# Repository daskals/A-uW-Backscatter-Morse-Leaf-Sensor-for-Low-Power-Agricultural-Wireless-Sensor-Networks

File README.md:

# A uW Backscatter-Morse-Leaf Sensor for Low-Power Agricultural Wireless Sensor Networks
Design files of IEEE publication: A uW Backscatter-Morse-Leaf Sensor for Low-Power Agricultural Wireless Sensor Networks

Nowadays, the monitoring of plant water stress
is of high importance in smart agriculture. Instead of the
traditional ground soil-moisture measurement, leaf sensing is a
new technology, which is used for the detection of plants needing
water. In this work, a novel, low-cost and low-power system for
leaf sensing using a new plant backscatter sensor node/tag is
presented. The latter, can result in the prevention of water waste
(water-use efficiency), when is connected to an irrigation system.
Specifically, the sensor measures the temperature differential
between the leaf and the air, which is directly related to the plant
water stress. Next, the tag collects the information from the leaf
sensor through an analog-to-digital converter (ADC), and then,
communicates remotely with a low-cost software-defined radio
(SDR) reader using monostatic backscatter architecture. The tag
consists of the sensor board, a microcontroller, an external timer
and an RF front-end for communication. The timer produces a
subcarrier frequency for simultaneous access of multiple tags.
The proposed work could be scaled and be a part of a large
backscatter wireless sensor network (WSN). The communication
protocol exploits the low-complexity Morse code modulation on
a 868 MHz carrier signal. The presented novel proof-of-consent
prototype is batteryless and was powered by a flexible solar panel
consuming power around 20 µW. The performance was validated
in an indoors environment where wireless communication was
successfully achieved up to 2 m distance.

**Authors:**

Spyridon Nektarios Daskalakis\
Stylianos D. Assimonis\
George Goussetis\
Manos M. Tentzeris\
Apostolos Georgiadis

---
IEEE Xplore: https://ieeexplore.ieee.org/document/8423620 \
Local: http://daskalakispiros.com/files/daskalalakis_sensors_2018.pdf

---

---
**Questions/issues**
Inquiries regarding the scripts provided are cordially welcome.

---
**Citing**

If you use our design, please cite [[1]](https://ieeexplore.ieee.org/document/8423620).

```bibtex
@article{daskalakis2018uw,
  title={A uW backscatter-morse-leaf sensor for low-power agricultural wireless sensor networks},
  author={Daskalakis, Spyridon Nektarios and Goussetis, George and Assimonis, Stylianos D and Tentzeris, Manos M and Georgiadis, Apostolos},
  journal={IEEE Sensors Journal},
  volume={18},
  number={19},
  pages={7889--7898},
  year={2018},
  publisher={IEEE}
}
 
```

[[1]](https://ieeexplore.ieee.org/document/8423620) S. N. Daskalakis, G. Goussetis, S. D. Assimonis, M. M. Tentzeris and A. Georgiadis, A uW Backscatter-Morse-Leaf Sensor for Low Power Agricultural Wireless Sensor Networks, IEEE Sensors Journal, Vol. 18, No. 19, pp. 7889–7898, Oct. 2018.

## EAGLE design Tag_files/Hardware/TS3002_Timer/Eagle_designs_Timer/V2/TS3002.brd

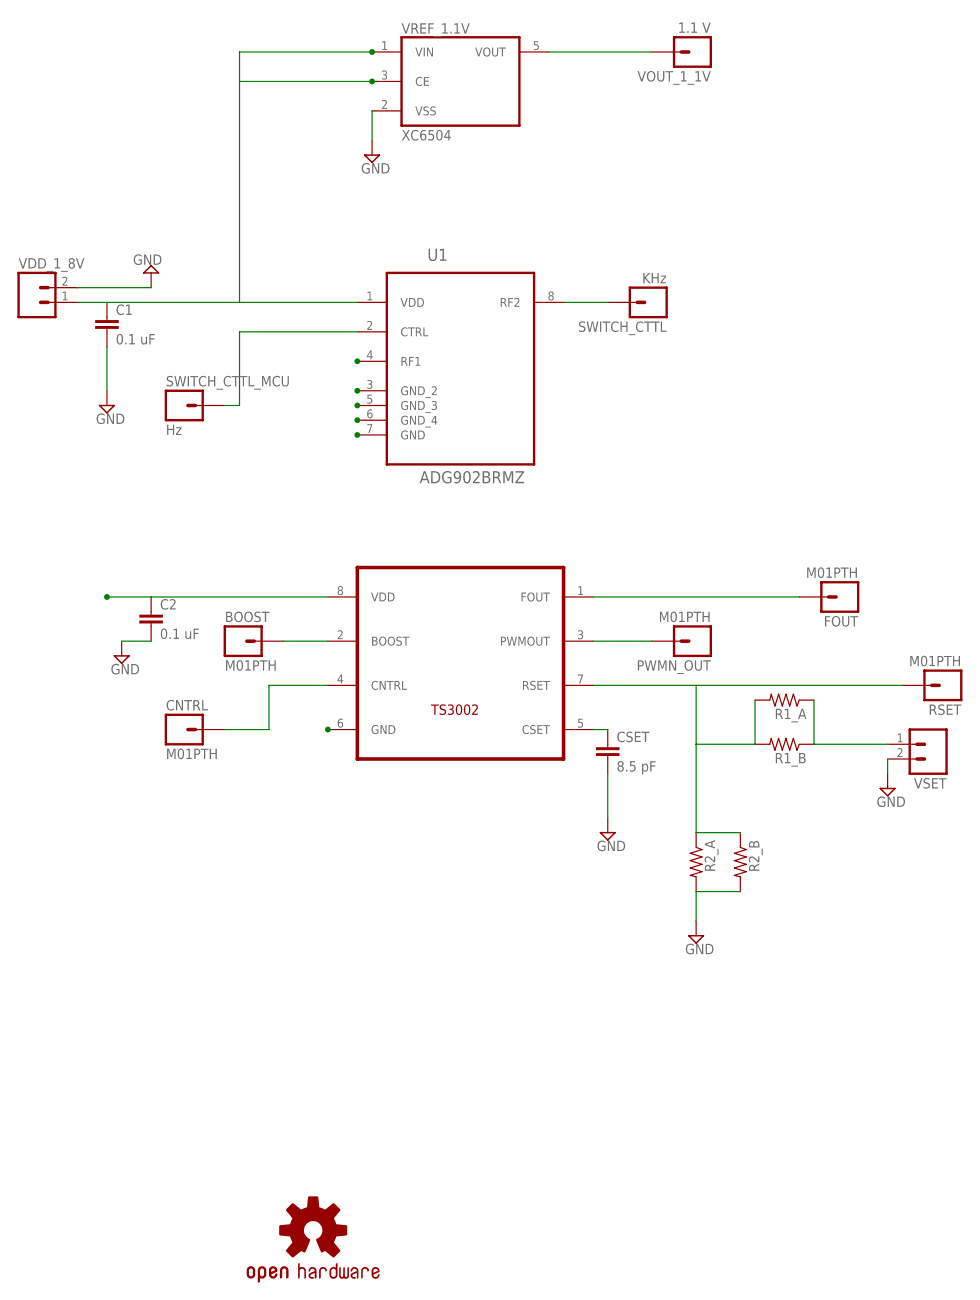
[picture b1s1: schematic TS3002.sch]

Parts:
BOOST: M01PTH; 1X01
C1, C2: 0.1 uF; 0603-CAP
CNTRL: M01PTH; 1X01
CSET: 8.5 pF; 0603-CAP
FOUT: M01PTH; 1X01
LOGO1: OSHW-LOGOL; OSHW-LOGO-L
PWMN_OUT: M01PTH; 1X01
R1_A, R1_B, R2_A, R2_B: RESISTOR0603-RES; 0603-RES
RSET: M01PTH; 1X01
SWITCH_CTTL: KHz; 1X01
SWITCH_CTTL_MCU: Hz; 1X01
U1: ADG902BRMZ; SOP65P490X110-8N
U$1: TS3002; TDFN22-8
VDD_1_8V: M02PTH; 1X02
VOUT_1_1V: 1.1 V; 1X01
VREF_1.1V: XC6504; SOT23-5
VSET: M02PTH; 1X02

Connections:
1_2OUT: C2.1, U$1.8 (VDD), VOUT_1_1V.1, VREF_1.1V.5 (VOUT)
GND: C1.2, C2.2, CSET.2, R2_A.2, R2_B.2, U1.3 (GND_2), U1.5 (GND_3), U1.6 (GND_4), U1.7 (GND), U$1.6 (GND), VDD_1_8V.2, VREF_1.1V.2 (VSS), VSET.2
unnamed: R1_A.1, R1_B.1, VSET.1
unnamed: SWITCH_CTTL_MCU.1, U1.2 (CTRL)
unnamed: BOOST.1, U$1.2 (BOOST)
unnamed: SWITCH_CTTL.1, U1.8 (RF2)
unnamed: CNTRL.1, U$1.4 (CNTRL)
unnamed: R1_A.2, R1_B.2, R2_A.1, R2_B.1, RSET.1, U$1.7 (RSET)
unnamed: PWMN_OUT.1, U$1.3 (PWMOUT)
unnamed: CSET.1, U$1.5 (CSET)
TIMER: FOUT.1, U1.4 (RF1), U$1.1 (FOUT)
VDD_1.8V1: C1.1, U1.1 (VDD), VDD_1_8V.1, VREF_1.1V.1 (VIN), VREF_1.1V.3 (CE)

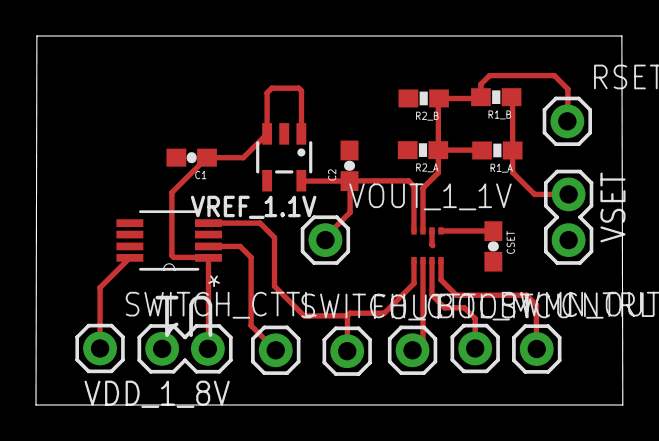
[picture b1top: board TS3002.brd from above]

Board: 2 copper layers, 32.6 x 20.5 mm, 21 parts (0 on the bottom side), 12 nets.

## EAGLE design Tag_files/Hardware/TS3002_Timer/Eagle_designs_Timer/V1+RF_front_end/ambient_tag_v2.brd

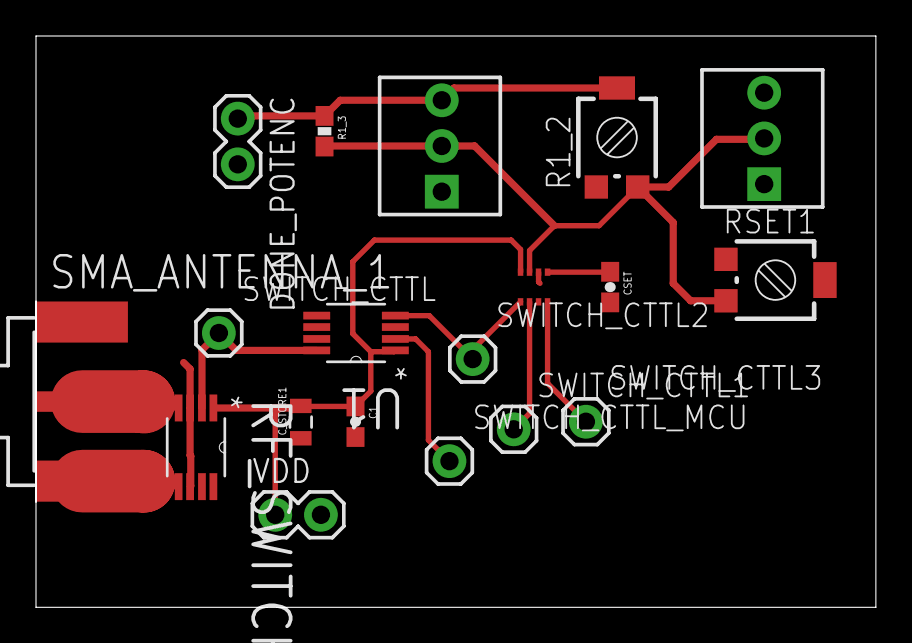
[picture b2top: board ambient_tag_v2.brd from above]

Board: 2 copper layers, 46.7 x 31.7 mm, 20 parts (0 on the bottom side), 12 nets.

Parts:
C1: 0.1 uF; 0603-CAP
CSET: 8.5 pF; 0603-CAP
C_STORE1: 4.7uF; 0805
DONE_POTENC: 1X02
LOGO1: OSHW-LOGOL; OSHW-LOGO-L
R1, R2: TRIMPOT; 3362U-2
R1_2: RTRIM3314G
R1_3: 0603-RES
RF_SWITCH: ADG919BRMZ; SOP65P490X110-8N
RSET1: RTRIM3314G
SMA_ANTENNA_1: SMA-142-0701-881/886; J502-ND-142-0701-881/886
SWITCH_CTTL, SWITCH_CTTL1, SWITCH_CTTL2, SWITCH_CTTL3: M01PTH; 1X01
SWITCH_CTTL_MCU: M01PTH; 1X01
U1: ADG902BRMZ; SOP65P490X110-8N
U$1: TDFN22-8
VDD: 1X02

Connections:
CTRL: SWITCH_CTTL3.1, U$1.4
GND: C1.2, CSET.2, C_STORE1.1, DONE_POTENC.2, R1.1, RF_SWITCH.3, RF_SWITCH.6, RF_SWITCH.7, RSET1.2, U1.3, U1.5, U1.6, U1.7, U$1.6, VDD.2
unnamed: DONE_POTENC.1, R1_2.2, R1_3.1, R2.3
unnamed: SWITCH_CTTL_MCU.1, U1.2
unnamed: SWITCH_CTTL1.1, U$1.2
unnamed: R1.2, R1_2.1, R1_3.2, R2.2, RSET1.1, U$1.7
unnamed: CSET.1, U$1.5
RF2: RF_SWITCH.5, SMA_ANTENNA_1.G@1, SMA_ANTENNA_1.G@2, SMA_ANTENNA_1.G@3, SMA_ANTENNA_1.G@4
RFC: RF_SWITCH.4, SMA_ANTENNA_1.1
SWITCH_CTTL: RF_SWITCH.2, SWITCH_CTTL.1, U1.8
TIMER: SWITCH_CTTL2.1, U1.4, U$1.1
VDD_1.8V: C1.1, C_STORE1.2, RF_SWITCH.1, U1.1, U$1.8, VDD.1

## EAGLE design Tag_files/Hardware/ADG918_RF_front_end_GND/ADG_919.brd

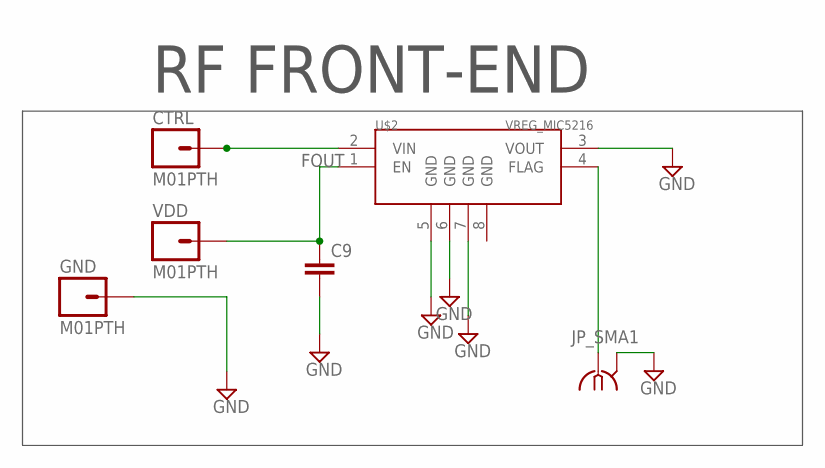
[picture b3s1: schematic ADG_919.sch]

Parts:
C9: CAP0603-CAP; 0603-CAP
CTRL: M01PTH; 1X01
GND: M01PTH; 1X01
JP_SMA1: SMA-142-0701-881/886; J502-ND-142-0701-881/886
U$2: VREG_MIC5216; MSOP8
VDD: M01PTH; 1X01

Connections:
FOUT: CTRL.1, U$2.2 (VIN)
GND: C9.2, GND.1, JP_SMA1.G@1 (2), JP_SMA1.G@2 (2), JP_SMA1.G@3 (2), JP_SMA1.G@4 (2), U$2.3 (VOUT), U$2.5 (GND), U$2.6 (GND), U$2.7 (GND)
unnamed: C9.1, U$2.1 (EN), VDD.1
unnamed: JP_SMA1.1, U$2.4 (FLAG)

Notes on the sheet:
RF FRONT-END

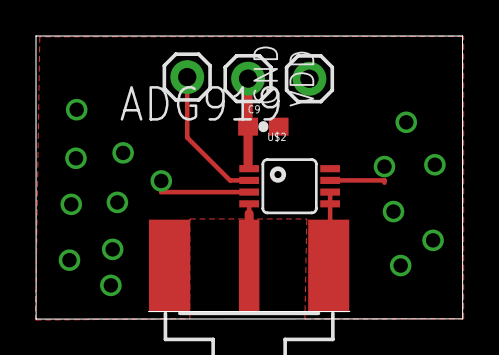
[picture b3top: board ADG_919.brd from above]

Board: 2 copper layers, 23.7 x 15.7 mm, 6 parts (0 on the bottom side), 4 nets.

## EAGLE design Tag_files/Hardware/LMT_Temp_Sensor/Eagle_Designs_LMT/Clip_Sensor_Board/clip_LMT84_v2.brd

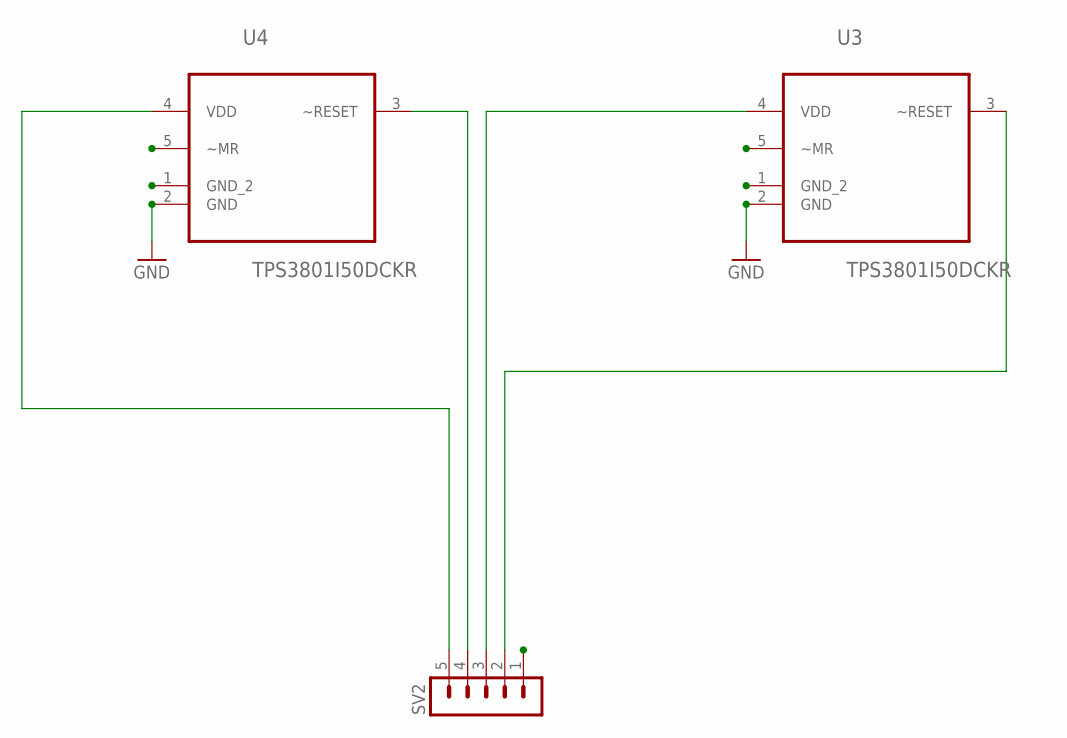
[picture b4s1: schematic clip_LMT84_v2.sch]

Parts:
SV2: MA05-1
U3, U4: TPS3801I50DCKR; SOT65P210X110-5N

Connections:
GND: SV2.1, U3.1 (GND_2), U3.2 (GND), U3.5 (~MR), U4.1 (GND_2), U4.2 (GND), U4.5 (~MR)
unnamed: SV2.3, U3.4 (VDD)
unnamed: SV2.5, U4.4 (VDD)
unnamed: SV2.4, U4.3 (~RESET)
VOUT_AIR: SV2.2, U3.3 (~RESET)

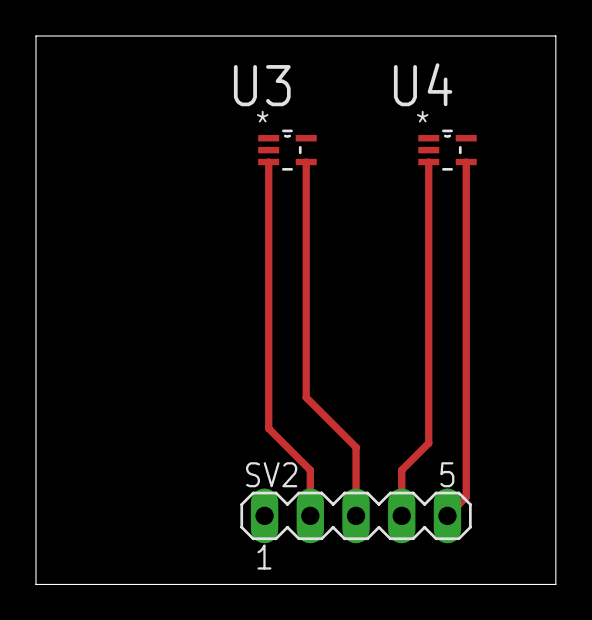
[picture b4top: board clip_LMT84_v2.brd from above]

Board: 2 copper layers, 28.9 x 30.5 mm, 3 parts (0 on the bottom side), 5 nets.

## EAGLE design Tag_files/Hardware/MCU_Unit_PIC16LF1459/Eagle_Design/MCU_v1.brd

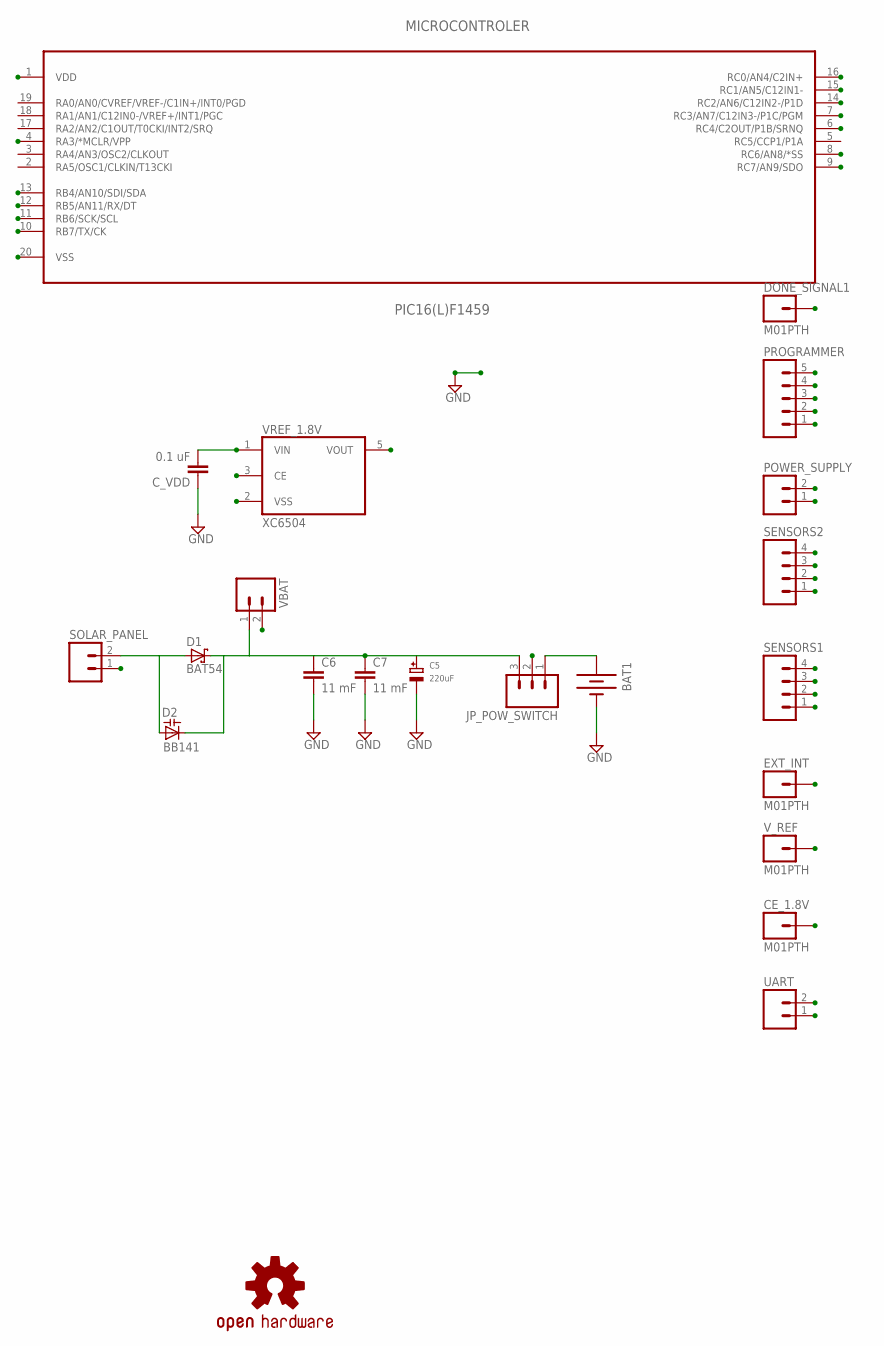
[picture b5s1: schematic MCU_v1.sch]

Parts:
BAT1: BATTERY20PTH_LAB; BATTCOM_20MM_PTH
C5: 220uF; EIA7343-31/D-R
C6, C7: 11 mF; 1210
CE_1.8V: M01PTH; 1X01
C_VDD: 0.1 uF; 0603-CAP
D1: BAT54; SOT23
D2: BB141; SOD523
DONE_SIGNAL1: M01PTH; 1X01
EXT_INT: M01PTH; 1X01
JP_POW_SWITCH: M03LOCK; 1X03_LOCK
LOGO1: OSHW-LOGOL; OSHW-LOGO-L
MICROCONTROLER: PIC16(L)F1459; SOP65P780X200-20N
POWER_SUPPLY: M02PTH; 1X02
PROGRAMMER: M05PTH; 1X05
SENSORS1, SENSORS2: M04LOCK; 1X04_LOCK
SOLAR_PANEL: M02PTH; 1X02
UART: M02PTH; 1X02
VBAT: M02PTH; 1X02
VREF_1.8V: XC6504; SOT23-5
V_REF: M01PTH; 1X01

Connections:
CE: CE_1.8V.1, VREF_1.8V.3 (CE)
DAC1: MICROCONTROLER.14 (RC2/AN6/C12IN2-/P1D), SENSORS2.4
DEL: C5.+, C6.1, C7.1, D1.3 (C), D2.C, JP_POW_SWITCH.3, VBAT.1
DONE_OUT: DONE_SIGNAL1.1, MICROCONTROLER.7 (RC3/AN7/C12IN3-/P1C/PGM)
GND: BAT1.2 (-), C5.-, C6.2, C7.2, C_VDD.1, MICROCONTROLER.20 (VSS), POWER_SUPPLY.1, PROGRAMMER.3, SENSORS1.1, SENSORS1.3, SOLAR_PANEL.1, UART.2, VBAT.2, VREF_1.8V.2 (VSS)
MCLR: MICROCONTROLER.4 (RA3/*MCLR/VPP), PROGRAMMER.5
unnamed: BAT1.1 (+), JP_POW_SWITCH.1
RB4: MICROCONTROLER.13 (RB4/AN10/SDI/SDA), SENSORS2.3
RB5: MICROCONTROLER.12 (RB5/AN11/RX/DT), SENSORS2.2
RB6: MICROCONTROLER.11 (RB6/SCK/SCL), SENSORS2.1
SENSOR1: MICROCONTROLER.8 (RC6/AN8/*SS), SENSORS1.4
SENSOR2: MICROCONTROLER.9 (RC7/AN9/SDO), SENSORS1.2
SOLAR_CELL: D1.1 (A), D2.A, SOLAR_PANEL.2
SPCLK: EXT_INT.1, MICROCONTROLER.15 (RC1/AN5/C12IN1-), PROGRAMMER.1
SPDAT: MICROCONTROLER.16 (RC0/AN4/C2IN+), PROGRAMMER.2, V_REF.1
SWITCH_CTTL: MICROCONTROLER.6 (RC4/C2OUT/P1B/SRNQ)
UART_TX: MICROCONTROLER.10 (RB7/TX/CK), UART.1
VDD: C_VDD.2, JP_POW_SWITCH.2, VREF_1.8V.1 (VIN)
VDD_1.8V: MICROCONTROLER.1 (VDD), POWER_SUPPLY.2, PROGRAMMER.4, VREF_1.8V.5 (VOUT)

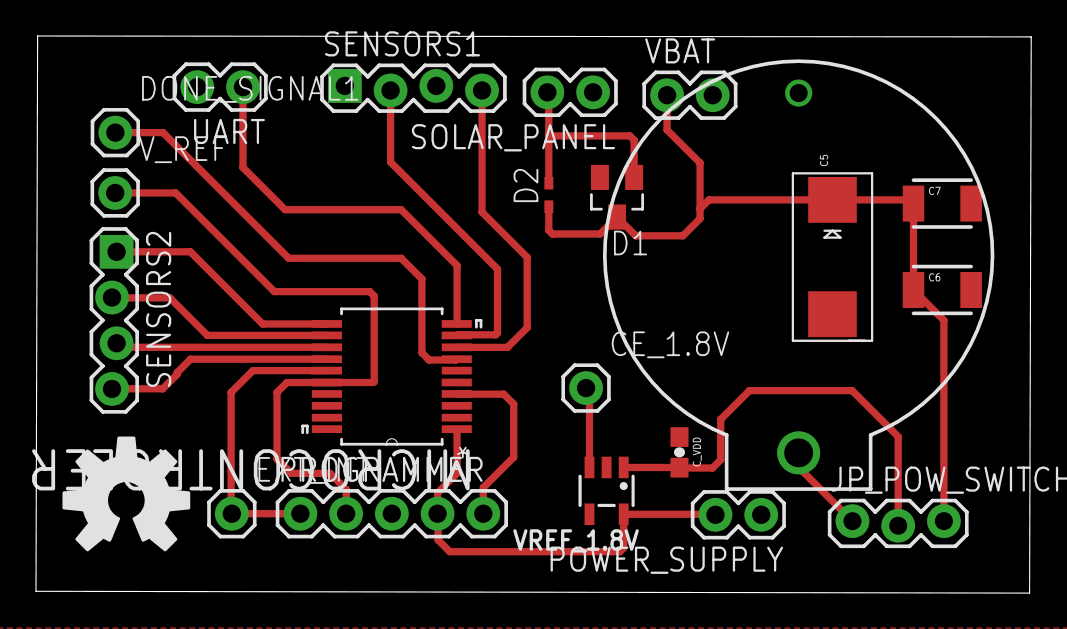
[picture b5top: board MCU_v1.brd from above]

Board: 2 copper layers, 55.3 x 31.0 mm, 22 parts (0 on the bottom side), 18 nets.

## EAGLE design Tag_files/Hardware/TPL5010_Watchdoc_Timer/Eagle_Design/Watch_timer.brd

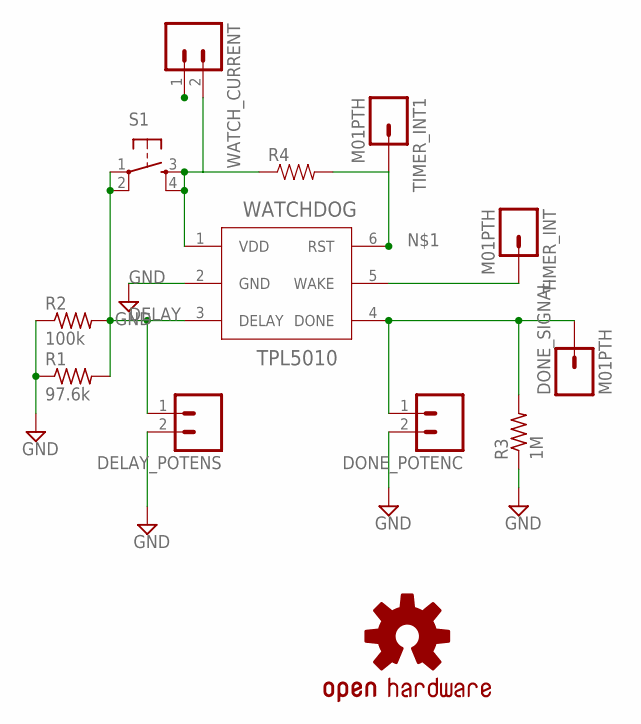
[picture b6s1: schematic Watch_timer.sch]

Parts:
DELAY_POTENS: M02PTH; 1X02
DONE_POTENC: M02PTH; 1X02
DONE_SIGNAL: M01PTH; 1X01
LOGO1: OSHW-LOGOL; OSHW-LOGO-L
R1: 97.6k; R0805
R2: 100k; R0805
R3: 1M; R0805
R4: RESISTOR0603-RES; 0603-RES
S1: TAC_SWITCHSMD; TACTILE_SWITCH_SMD
TIMER_INT, TIMER_INT1: M01PTH; 1X01
WATCHDOG: TPL5010; TSOT-23
WATCH_CURRENT: M02PTH; 1X02

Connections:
DELAY: DELAY_POTENS.1, R1.2, R2.2, S1.1, S1.2, WATCHDOG.3 (DELAY)
DONE: DONE_POTENC.1, DONE_SIGNAL.1, R3.2, WATCHDOG.4 (DONE)
GND: DELAY_POTENS.2, DONE_POTENC.2, R1.1, R2.1, R3.1, WATCHDOG.2 (GND)
unnamed: R4.2, TIMER_INT1.1, WATCHDOG.6 (RST)
unnamed: TIMER_INT.1, WATCHDOG.5 (WAKE)
VDD: WATCH_CURRENT.1
VDD_WATCH: R4.1, S1.3, S1.4, WATCHDOG.1 (VDD), WATCH_CURRENT.2

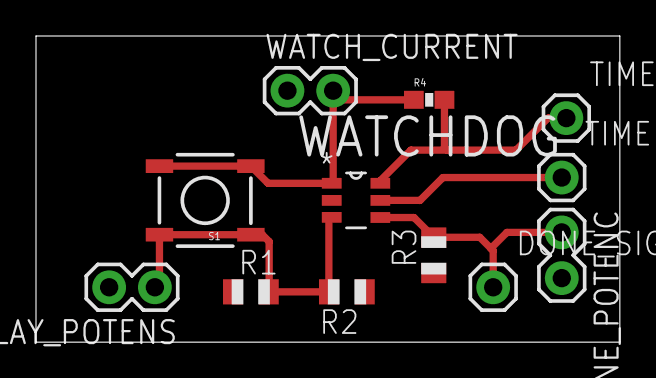
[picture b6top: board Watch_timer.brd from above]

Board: 2 copper layers, 32.4 x 17.0 mm, 13 parts (0 on the bottom side), 6 nets.

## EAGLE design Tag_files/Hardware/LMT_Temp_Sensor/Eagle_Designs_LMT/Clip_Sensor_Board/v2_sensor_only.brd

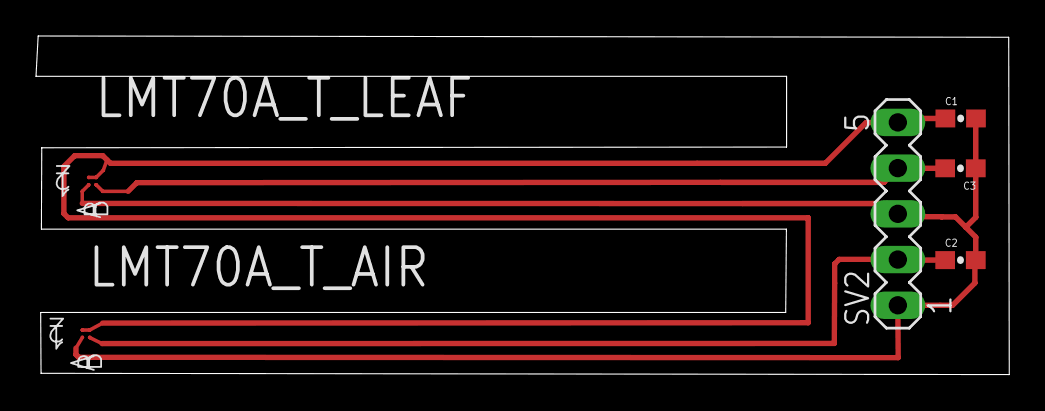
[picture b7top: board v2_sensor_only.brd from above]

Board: 2 copper layers, 54.1 x 18.8 mm, 6 parts (0 on the bottom side), 4 nets.

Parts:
C1: 0.1uF; 0603-CAP
C2, C3: 100 pF; 0603-CAP
LMT70A_T_AIR, LMT70A_T_LEAF: INA216A1YFFR; BGA4C40P2X2_76X76X63
SV2: MA05-1

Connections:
GND_A: C1.2, C2.2, C3.1, LMT70A_T_AIR.A1, LMT70A_T_LEAF.A1, SV2.1, SV2.3
VDD_A: C1.1, LMT70A_T_AIR.A2, LMT70A_T_AIR.B2, LMT70A_T_LEAF.A2, LMT70A_T_LEAF.B2, SV2.5
VOUT_AIR: C2.1, LMT70A_T_AIR.B1, SV2.2
VOUT_LEAF: C3.2, LMT70A_T_LEAF.B1, SV2.4

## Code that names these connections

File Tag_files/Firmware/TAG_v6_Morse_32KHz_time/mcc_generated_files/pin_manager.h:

/**
  @Generated Pin Manager Header File

  @Company:
    Microchip Technology Inc.

  @File Name:
    pin_manager.h

  @Summary:
    This is the Pin Manager file generated using MPLAB(c) Code Configurator

  @Description:
    This header file provides implementations for pin APIs for all pins selected in the GUI.
    Generation Information :
        Product Revision  :  MPLAB(c) Code Configurator - 4.26
        Device            :  PIC16LF1459
        Version           :  1.01
    The generated drivers are tested against the following:
        Compiler          :  XC8 1.35
        MPLAB             :  MPLAB X 3.40

    Copyright (c) 2013 - 2015 released Microchip Technology Inc.  All rights reserved.

    Microchip licenses to you the right to use, modify, copy and distribute
    Software only when embedded on a Microchip microcontroller or digital signal
    controller that is integrated into your product or third party product
    (pursuant to the sublicense terms in the accompanying license agreement).

    You should refer to the license agreement accompanying this Software for
    additional information regarding your rights and obligations.

    SOFTWARE AND DOCUMENTATION ARE PROVIDED "AS IS" WITHOUT WARRANTY OF ANY KIND,
    EITHER EXPRESS OR IMPLIED, INCLUDING WITHOUT LIMITATION, ANY WARRANTY OF
    MERCHANTABILITY, TITLE, NON-INFRINGEMENT AND FITNESS FOR A PARTICULAR PURPOSE.
    IN NO EVENT SHALL MICROCHIP OR ITS LICENSORS BE LIABLE OR OBLIGATED UNDER
    CONTRACT, NEGLIGENCE, STRICT LIABILITY, CONTRIBUTION, BREACH OF WARRANTY, OR
    OTHER LEGAL EQUITABLE THEORY ANY DIRECT OR INDIRECT DAMAGES OR EXPENSES
    INCLUDING BUT NOT LIMITED TO ANY INCIDENTAL, SPECIAL, INDIRECT, PUNITIVE OR
    CONSEQUENTIAL DAMAGES, LOST PROFITS OR LOST DATA, COST OF PROCUREMENT OF
    SUBSTITUTE GOODS, TECHNOLOGY, SERVICES, OR ANY CLAIMS BY THIRD PARTIES
    (INCLUDING BUT NOT LIMITED TO ANY DEFENSE THEREOF), OR OTHER SIMILAR COSTS.

*/


#ifndef PIN_MANAGER_H
#define PIN_MANAGER_H

#define INPUT   1
#define OUTPUT  0

#define HIGH    1
#define LOW     0

#define ANALOG      1
#define DIGITAL     0

#define PULL_UP_ENABLED      1
#define PULL_UP_DISABLED     0

// get/set IO_RB4 aliases
#define IO_RB4_TRIS               TRISBbits.TRISB4
#define IO_RB4_LAT                LATBbits.LATB4
#define IO_RB4_PORT               PORTBbits.RB4
#define IO_RB4_WPU                WPUBbits.WPUB4
#define IO_RB4_ANS                ANSELBbits.ANSB4
#define IO_RB4_SetHigh()            do { LATBbits.LATB4 = 1; } while(0)
#define IO_RB4_SetLow()             do { LATBbits.LATB4 = 0; } while(0)
#define IO_RB4_Toggle()             do { LATBbits.LATB4 = ~LATBbits.LATB4; } while(0)
#define IO_RB4_GetValue()           PORTBbits.RB4
#define IO_RB4_SetDigitalInput()    do { TRISBbits.TRISB4 = 1; } while(0)
#define IO_RB4_SetDigitalOutput()   do { TRISBbits.TRISB4 = 0; } while(0)
#define IO_RB4_SetPullup()      do { WPUBbits.WPUB4 = 1; } while(0)
#define IO_RB4_ResetPullup()    do { WPUBbits.WPUB4 = 0; } while(0)
#define IO_RB4_SetAnalogMode()  do { ANSELBbits.ANSB4 = 1; } while(0)
#define IO_RB4_SetDigitalMode() do { ANSELBbits.ANSB4 = 0; } while(0)

// get/set RC0 procedures
#define RC0_SetHigh()    do { LATCbits.LATC0 = 1; } while(0)
#define RC0_SetLow()   do { LATCbits.LATC0 = 0; } while(0)
#define RC0_Toggle()   do { LATCbits.LATC0 = ~LATCbits.LATC0; } while(0)
#define RC0_GetValue()         PORTCbits.RC0
#define RC0_SetDigitalInput()   do { TRISCbits.TRISC0 = 1; } while(0)
#define RC0_SetDigitalOutput()  do { TRISCbits.TRISC0 = 0; } while(0)
#define RC0_SetAnalogMode() do { ANSELCbits.ANSC0 = 1; } while(0)
#define RC0_SetDigitalMode()do { ANSELCbits.ANSC0 = 0; } while(0)

// get/set RC1 procedures
#define RC1_SetHigh()    do { LATCbits.LATC1 = 1; } while(0)
#define RC1_SetLow()   do { LATCbits.LATC1 = 0; } while(0)
#define RC1_Toggle()   do { LATCbits.LATC1 = ~LATCbits.LATC1; } while(0)
#define RC1_GetValue()         PORTCbits.RC1
#define RC1_SetDigitalInput()   do { TRISCbits.TRISC1 = 1; } while(0)
#define RC1_SetDigitalOutput()  do { TRISCbits.TRISC1 = 0; } while(0)
#define RC1_SetAnalogMode() do { ANSELCbits.ANSC1 = 1; } while(0)
#define RC1_SetDigitalMode()do { ANSELCbits.ANSC1 = 0; } while(0)

// get/set RC2 procedures
#define RC2_SetHigh()    do { LATCbits.LATC2 = 1; } while(0)
#define RC2_SetLow()   do { LATCbits.LATC2 = 0; } while(0)
#define RC2_Toggle()   do { LATCbits.LATC2 = ~LATCbits.LATC2; } while(0)
#define RC2_GetValue()         PORTCbits.RC2
#define RC2_SetDigitalInput()   do { TRISCbits.TRISC2 = 1; } while(0)
#define RC2_SetDigitalOutput()  do { TRISCbits.TRISC2 = 0; } while(0)
#define RC2_SetAnalogMode() do { ANSELCbits.ANSC2 = 1; } while(0)
#define RC2_SetDigitalMode()do { ANSELCbits.ANSC2 = 0; } while(0)

// get/set IO_RC3 aliases
#define IO_RC3_TRIS               TRISCbits.TRISC3
#define IO_RC3_LAT                LATCbits.LATC3
#define IO_RC3_PORT               PORTCbits.RC3
#define IO_RC3_ANS                ANSELCbits.ANSC3
#define IO_RC3_SetHigh()            do { LATCbits.LATC3 = 1; } while(0)
#define IO_RC3_SetLow()             do { LATCbits.LATC3 = 0; } while(0)
#define IO_RC3_Toggle()             do { LATCbits.LATC3 = ~LATCbits.LATC3; } while(0)
#define IO_RC3_GetValue()           PORTCbits.RC3
#define IO_RC3_SetDigitalInput()    do { TRISCbits.TRISC3 = 1; } while(0)
#define IO_RC3_SetDigitalOutput()   do { TRISCbits.TRISC3 = 0; } while(0)
#define IO_RC3_SetAnalogMode()  do { ANSELCbits.ANSC3 = 1; } while(0)
#define IO_RC3_SetDigitalMode() do { ANSELCbits.ANSC3 = 0; } while(0)

// get/set channel_AN8 aliases
#define channel_AN8_TRIS               TRISCbits.TRISC6
#define channel_AN8_LAT                LATCbits.LATC6
#define channel_AN8_PORT               PORTCbits.RC6
#define channel_AN8_ANS                ANSELCbits.ANSC6
#define channel_AN8_SetHigh()            do { LATCbits.LATC6 = 1; } while(0)
#define channel_AN8_SetLow()             do { LATCbits.LATC6 = 0; } while(0)
#define channel_AN8_Toggle()             do { LATCbits.LATC6 = ~LATCbits.LATC6; } while(0)
#define channel_AN8_GetValue()           PORTCbits.RC6
#define channel_AN8_SetDigitalInput()    do { TRISCbits.TRISC6 = 1; } while(0)
#define channel_AN8_SetDigitalOutput()   do { TRISCbits.TRISC6 = 0; } while(0)
#define channel_AN8_SetAnalogMode()  do { ANSELCbits.ANSC6 = 1; } while(0)
#define channel_AN8_SetDigitalMode() do { ANSELCbits.ANSC6 = 0; } while(0)

// get/set channel_AN9 aliases
#define channel_AN9_TRIS               TRISCbits.TRISC7
#define channel_AN9_LAT                LATCbits.LATC7
#define channel_AN9_PORT               PORTCbits.RC7
#define channel_AN9_ANS                ANSELCbits.ANSC7
#define channel_AN9_SetHigh()            do { LATCbits.LATC7 = 1; } while(0)
#define channel_AN9_SetLow()             do { LATCbits.LATC7 = 0; } while(0)
#define channel_AN9_Toggle()             do { LATCbits.LATC7 = ~LATCbits.LATC7; } while(0)
#define channel_AN9_GetValue()           PORTCbits.RC7
#define channel_AN9_SetDigitalInput()    do { TRISCbits.TRISC7 = 1; } while(0)
#define channel_AN9_SetDigitalOutput()   do { TRISCbits.TRISC7 = 0; } while(0)
#define channel_AN9_SetAnalogMode()  do { ANSELCbits.ANSC7 = 1; } while(0)
#define channel_AN9_SetDigitalMode() do { ANSELCbits.ANSC7 = 0; } while(0)

/**
   @Param
    none
   @Returns
    none
   @Description
    GPIO and peripheral I/O initialization
   @Example
    PIN_MANAGER_Initialize();
 */
void PIN_MANAGER_Initialize (void);

/**
 * @Param
    none
 * @Returns
    none
 * @Description
    Interrupt on Change Handling routine
 * @Example
    PIN_MANAGER_IOC();
 */
void PIN_MANAGER_IOC(void);



#endif // PIN_MANAGER_H
/**
 End of File
*/

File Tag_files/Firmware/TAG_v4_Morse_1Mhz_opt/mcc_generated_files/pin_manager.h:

/**
  @Generated Pin Manager Header File

  @Company:
    Microchip Technology Inc.

  @File Name:
    pin_manager.h

  @Summary:
    This is the Pin Manager file generated using MPLAB(c) Code Configurator

  @Description:
    This header file provides implementations for pin APIs for all pins selected in the GUI.
    Generation Information :
        Product Revision  :  MPLAB(c) Code Configurator - 4.26
        Device            :  PIC16LF1459
        Version           :  1.01
    The generated drivers are tested against the following:
        Compiler          :  XC8 1.35
        MPLAB             :  MPLAB X 3.40

    Copyright (c) 2013 - 2015 released Microchip Technology Inc.  All rights reserved.

    Microchip licenses to you the right to use, modify, copy and distribute
    Software only when embedded on a Microchip microcontroller or digital signal
    controller that is integrated into your product or third party product
    (pursuant to the sublicense terms in the accompanying license agreement).

    You should refer to the license agreement accompanying this Software for
    additional information regarding your rights and obligations.

    SOFTWARE AND DOCUMENTATION ARE PROVIDED "AS IS" WITHOUT WARRANTY OF ANY KIND,
    EITHER EXPRESS OR IMPLIED, INCLUDING WITHOUT LIMITATION, ANY WARRANTY OF
    MERCHANTABILITY, TITLE, NON-INFRINGEMENT AND FITNESS FOR A PARTICULAR PURPOSE.
    IN NO EVENT SHALL MICROCHIP OR ITS LICENSORS BE LIABLE OR OBLIGATED UNDER
    CONTRACT, NEGLIGENCE, STRICT LIABILITY, CONTRIBUTION, BREACH OF WARRANTY, OR
    OTHER LEGAL EQUITABLE THEORY ANY DIRECT OR INDIRECT DAMAGES OR EXPENSES
    INCLUDING BUT NOT LIMITED TO ANY INCIDENTAL, SPECIAL, INDIRECT, PUNITIVE OR
    CONSEQUENTIAL DAMAGES, LOST PROFITS OR LOST DATA, COST OF PROCUREMENT OF
    SUBSTITUTE GOODS, TECHNOLOGY, SERVICES, OR ANY CLAIMS BY THIRD PARTIES
    (INCLUDING BUT NOT LIMITED TO ANY DEFENSE THEREOF), OR OTHER SIMILAR COSTS.

*/


#ifndef PIN_MANAGER_H
#define PIN_MANAGER_H

#define INPUT   1
#define OUTPUT  0

#define HIGH    1
#define LOW     0

#define ANALOG      1
#define DIGITAL     0

#define PULL_UP_ENABLED      1
#define PULL_UP_DISABLED     0

// get/set RB5 procedures
#define RB5_SetHigh()    do { LATBbits.LATB5 = 1; } while(0)
#define RB5_SetLow()   do { LATBbits.LATB5 = 0; } while(0)
#define RB5_Toggle()   do { LATBbits.LATB5 = ~LATBbits.LATB5; } while(0)
#define RB5_GetValue()         PORTBbits.RB5
#define RB5_SetDigitalInput()   do { TRISBbits.TRISB5 = 1; } while(0)
#define RB5_SetDigitalOutput()  do { TRISBbits.TRISB5 = 0; } while(0)
#define RB5_SetPullup()     do { WPUBbits.WPUB5 = 1; } while(0)
#define RB5_ResetPullup()   do { WPUBbits.WPUB5 = 0; } while(0)
#define RB5_SetAnalogMode() do { ANSELBbits.ANSB5 = 1; } while(0)
#define RB5_SetDigitalMode()do { ANSELBbits.ANSB5 = 0; } while(0)

// get/set RB7 procedures
#define RB7_SetHigh()    do { LATBbits.LATB7 = 1; } while(0)
#define RB7_SetLow()   do { LATBbits.LATB7 = 0; } while(0)
#define RB7_Toggle()   do { LATBbits.LATB7 = ~LATBbits.LATB7; } while(0)
#define RB7_GetValue()         PORTBbits.RB7
#define RB7_SetDigitalInput()   do { TRISBbits.TRISB7 = 1; } while(0)
#define RB7_SetDigitalOutput()  do { TRISBbits.TRISB7 = 0; } while(0)
#define RB7_SetPullup()     do { WPUBbits.WPUB7 = 1; } while(0)
#define RB7_ResetPullup()   do { WPUBbits.WPUB7 = 0; } while(0)

// get/set RC1 procedures
#define RC1_SetHigh()    do { LATCbits.LATC1 = 1; } while(0)
#define RC1_SetLow()   do { LATCbits.LATC1 = 0; } while(0)
#define RC1_Toggle()   do { LATCbits.LATC1 = ~LATCbits.LATC1; } while(0)
#define RC1_GetValue()         PORTCbits.RC1
#define RC1_SetDigitalInput()   do { TRISCbits.TRISC1 = 1; } while(0)
#define RC1_SetDigitalOutput()  do { TRISCbits.TRISC1 = 0; } while(0)
#define RC1_SetAnalogMode() do { ANSELCbits.ANSC1 = 1; } while(0)
#define RC1_SetDigitalMode()do { ANSELCbits.ANSC1 = 0; } while(0)

// get/set IO_RC3 aliases
#define IO_RC3_TRIS               TRISCbits.TRISC3
#define IO_RC3_LAT                LATCbits.LATC3
#define IO_RC3_PORT               PORTCbits.RC3
#define IO_RC3_ANS                ANSELCbits.ANSC3
#define IO_RC3_SetHigh()            do { LATCbits.LATC3 = 1; } while(0)
#define IO_RC3_SetLow()             do { LATCbits.LATC3 = 0; } while(0)
#define IO_RC3_Toggle()             do { LATCbits.LATC3 = ~LATCbits.LATC3; } while(0)
#define IO_RC3_GetValue()           PORTCbits.RC3
#define IO_RC3_SetDigitalInput()    do { TRISCbits.TRISC3 = 1; } while(0)
#define IO_RC3_SetDigitalOutput()   do { TRISCbits.TRISC3 = 0; } while(0)
#define IO_RC3_SetAnalogMode()  do { ANSELCbits.ANSC3 = 1; } while(0)
#define IO_RC3_SetDigitalMode() do { ANSELCbits.ANSC3 = 0; } while(0)

// get/set IO_RC4 aliases
#define IO_RC4_TRIS               TRISCbits.TRISC4
#define IO_RC4_LAT                LATCbits.LATC4
#define IO_RC4_PORT               PORTCbits.RC4
#define IO_RC4_SetHigh()            do { LATCbits.LATC4 = 1; } while(0)
#define IO_RC4_SetLow()             do { LATCbits.LATC4 = 0; } while(0)
#define IO_RC4_Toggle()             do { LATCbits.LATC4 = ~LATCbits.LATC4; } while(0)
#define IO_RC4_GetValue()           PORTCbits.RC4
#define IO_RC4_SetDigitalInput()    do { TRISCbits.TRISC4 = 1; } while(0)
#define IO_RC4_SetDigitalOutput()   do { TRISCbits.TRISC4 = 0; } while(0)

// get/set channel_AN8 aliases
#define channel_AN8_TRIS               TRISCbits.TRISC6
#define channel_AN8_LAT                LATCbits.LATC6
#define channel_AN8_PORT               PORTCbits.RC6
#define channel_AN8_ANS                ANSELCbits.ANSC6
#define channel_AN8_SetHigh()            do { LATCbits.LATC6 = 1; } while(0)
#define channel_AN8_SetLow()             do { LATCbits.LATC6 = 0; } while(0)
#define channel_AN8_Toggle()             do { LATCbits.LATC6 = ~LATCbits.LATC6; } while(0)
#define channel_AN8_GetValue()           PORTCbits.RC6
#define channel_AN8_SetDigitalInput()    do { TRISCbits.TRISC6 = 1; } while(0)
#define channel_AN8_SetDigitalOutput()   do { TRISCbits.TRISC6 = 0; } while(0)
#define channel_AN8_SetAnalogMode()  do { ANSELCbits.ANSC6 = 1; } while(0)
#define channel_AN8_SetDigitalMode() do { ANSELCbits.ANSC6 = 0; } while(0)

// get/set channel_AN9 aliases
#define channel_AN9_TRIS               TRISCbits.TRISC7
#define channel_AN9_LAT                LATCbits.LATC7
#define channel_AN9_PORT               PORTCbits.RC7
#define channel_AN9_ANS                ANSELCbits.ANSC7
#define channel_AN9_SetHigh()            do { LATCbits.LATC7 = 1; } while(0)
#define channel_AN9_SetLow()             do { LATCbits.LATC7 = 0; } while(0)
#define channel_AN9_Toggle()             do { LATCbits.LATC7 = ~LATCbits.LATC7; } while(0)
#define channel_AN9_GetValue()           PORTCbits.RC7
#define channel_AN9_SetDigitalInput()    do { TRISCbits.TRISC7 = 1; } while(0)
#define channel_AN9_SetDigitalOutput()   do { TRISCbits.TRISC7 = 0; } while(0)
#define channel_AN9_SetAnalogMode()  do { ANSELCbits.ANSC7 = 1; } while(0)
#define channel_AN9_SetDigitalMode() do { ANSELCbits.ANSC7 = 0; } while(0)

/**
   @Param
    none
   @Returns
    none
   @Description
    GPIO and peripheral I/O initialization
   @Example
    PIN_MANAGER_Initialize();
 */
void PIN_MANAGER_Initialize (void);

/**
 * @Param
    none
 * @Returns
    none
 * @Description
    Interrupt on Change Handling routine
 * @Example
    PIN_MANAGER_IOC();
 */
void PIN_MANAGER_IOC(void);



#endif // PIN_MANAGER_H
/**
 End of File
*/

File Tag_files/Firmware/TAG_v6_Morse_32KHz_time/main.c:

/*
Spiros Daskalakis 
Last Version: 31/1/2018
Email: daskalakispiros@gmail.com
Website: www.daskalakispiros.com
*/

#include <stdio.h>
#include <string.h>
#include "mcc_generated_files/mcc.h"
#include "BackscatterComm.h"
#include "main.h"
#include "pic16lf1459.h"
#include <math.h>


    
    char str8[10]=0;
    int delay=4;  
      int v;
    int NODE_ID=1;
    int SENSORID=0;
    int sleep=0;
    int sensor0=0;
    int sensor1=0;
void main(void)
{
 
  
    // initialize the device
    SYSTEM_Initialize();
    uint8_t count=0;
    
//FVR_Initialize();
  
    // When using interrupts, you need to set the Global and Peripheral Interrupt Enable bits
    // Use the following macros to:
    if (sleep==1)
    {    
       // Enable the Global Interrupts
       INTERRUPT_GlobalInterruptEnable();
    }
    else
    {
      // Disable the Global Interrupts
    INTERRUPT_GlobalInterruptDisable();
    }   
    
    //INTERRUPT_GlobalInterruptEnable();
        
    // Enable the Peripheral Interrupts
    //INTERRUPT_PeripheralInterruptEnable();

    // Disable the Peripheral Interrupts
    //INTERRUPT_PeripheralInterruptDisable();
   ADC_Initialize();
   DAC_Initialize();
     
   printf("Start\n");
    while (1)
    {
         
         DACEN=0;
         //LATC3=1;
         //leaf temp
         
         sensor0= ADC_GetConversion(channel_AN8); 
        
         
         //air temp
         sensor1= ADC_GetConversion(channel_AN9);
         
         //Close adc  
         ADCON0 = 0x00; 
         
         //sprintf(str8,"%dE%d", sensor0,sensor1);
        //sprintf(str8,"%dE%d", ADC_GetConversion(channel_AN8), ADC_GetConversion(channel_AN9));
         
         
         
         //LATC3=0;
       
        DACEN=0;  
        DACCON1  = 0 ; //mexri 31 paei  
        LATB4 = 1;
         
       sprintf(str8,"%dE%d", 2, 4);

       char *c = str8;
       for( ; *c ; c++ ) 
       {
            sendChar( *c );
       }
	
       DACEN=0;  // Close DAC 
       LATB4 = 0; // Close timer 
         if (sleep==1) { 
             
             
             SLEEP(); // go to sleep ->interupt at pin 15 
           }
       
       for(v = 0; v < 250; ++v)
	    {
		      _nop();
	   }
       
    
    }
    
}

void dot()
{
    int i;
    LATC3=1;
	
	for(i = 0; i < delay; ++i)
	{
		      _nop();
	}
     LATC3=0;
	 for(i = 0; i < delay; ++i)
	 {
	          _nop();
	 }
}

void dash()
{
    int i;
    LATC3=1;
	
	
		for(i = 0; i < delay; ++i)
		{
		      _nop();
		}
    for(i = 0; i < delay; ++i)
		{
		      _nop();
		}
		
    for(i = 0; i < delay; ++i)
		{
		      _nop();
		}

     LATC3=0;
	 for(i = 0; i < delay; ++i)
	 {
	          _nop();
	 }
}



void sendChar(unsigned char a)
{
 int i;
 if (a=='0'){
  dash();dash();dash();dash();dash();}
 else if  (a=='1'){
  dot(); dash(); dash(); dash(); dash();}
 else if  (a=='2'){
  dot();  dot(); dash(); dash(); dash();}
  else if  (a=='3'){
    dot();  dot(); dot(); dash(); dash();}
 else if  (a=='4'){
  dot(); dot(); dot(); dot(); dash();}
 else if  (a=='5'){
  dot();  dot(); dot(); dot(); dot();}
 else if  (a=='6'){
  dash(); dot(); dot(); dot(); dot();}
 else if  (a=='7'){
   dash(); dash();  dot(); dot(); dot();}
  else if  (a=='8'){
    dash();dash();dash();  dot(); dot(); }
 else if  (a=='9'){
     dash();dash();dash();dash(); dot();}
 else if  (a=='E'){
      dot();}
 
 //pause(2); // 3 dots between characters, 1 was already after the beep
 for(i = 0; i < delay; ++i){
         	  _nop();		     
         	}// gia na ftiaxo tous idios xronous
 for(i = 0; i < delay; ++i){
         	  _nop();

         	}// gia na ftiaxo tous idios xronous 
}

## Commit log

2021-10-15 Update tag folder
2021-10-15 update paper files
2021-10-15 Upload receiver files

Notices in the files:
parts and their libraries:
SparkFun-Capacitors: Licensing: CC v3.0 Share-Alike You are welcome to use this library for commercial purposes.
SparkFun-Capacitors: Licensing: Creative Commons ShareAlike 4.0 International - https://creativecommons.org/licenses/by-sa/4.0
torex: Copyright (C) 2015, Bob Starr
